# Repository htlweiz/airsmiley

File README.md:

# Air Smiley: eCO2 measurement box
A small-ish and simple box to measure
- eCO2 with a CCS811 sensor
- Temperature and Humidity with a DHT22 sensor

using a Wemos D1 mini (or clone) with visualization on a
- 0.96" I2C OLED (SSD1306 based)
- NeoPixel compatible RGB LED ring (WS2812B)

The thresholds are set according to [REHVA's recommendations for schools](https://www.rehva.eu/fileadmin/user_upload/REHVA_COVID-19_guidance_document_School_guidance_25112020.pdf).

## User Manual
A (german) user manual is available [here](AIR%20SMILEY.pdf).

## Burn-In
For full sensor accuracy, according to the [datasheet](https://www.sciosense.com/wp-content/uploads/2020/01/CCS811-Datasheet.pdf), the device first needs a "burn-in" phase of 48 operating hours. 

## Run-In
After the "burn-in" phase, the values are considered accurate after a "run-in" time of 20 minutes after power on. Make sure you expose the sensor to clean air throughout the run-in or shortly afterwards to correctly set the baseline (low CO2) for correct sensor readings.

## Flashing
- Install the newest [ESP8266 support](https://www.heise.de/ct/artikel/Arduino-IDE-installieren-und-fit-machen-fuer-ESP8266-und-ESP32-4130814.html)
- Add the following libraries (using the built-in library manager, *Tools –> Manage Libraries...*)
  - NeoPixelBus by Makuna (LGPL-3.0 License)
  - Adafruit CCS811 (MIT License)
  - DHT sensor library by Adafruit (MIT License)
  - Adafruit SSD1306 (BSD License)

## PCB
The PCB has been designed with KiCad and uses the corresponding [libraries](https://kicad.org/libraries/) which are available under the [Creative Commons CC-BY-SA 4.0 License](https://creativecommons.org/licenses/by-sa/4.0/legalcode). Additionally, a [footprint](https://github.com/rubienr/wemos-d1-mini-kicad) made by [rubienr](https://github.com/rubienr) is used.

The PCB is designed to be screwed into a case available at [aliexpress](https://de.aliexpress.com/item/4000068796385.html?spm=a2g0s.9042311.0.0.52614c4dDeY8Wv).

1

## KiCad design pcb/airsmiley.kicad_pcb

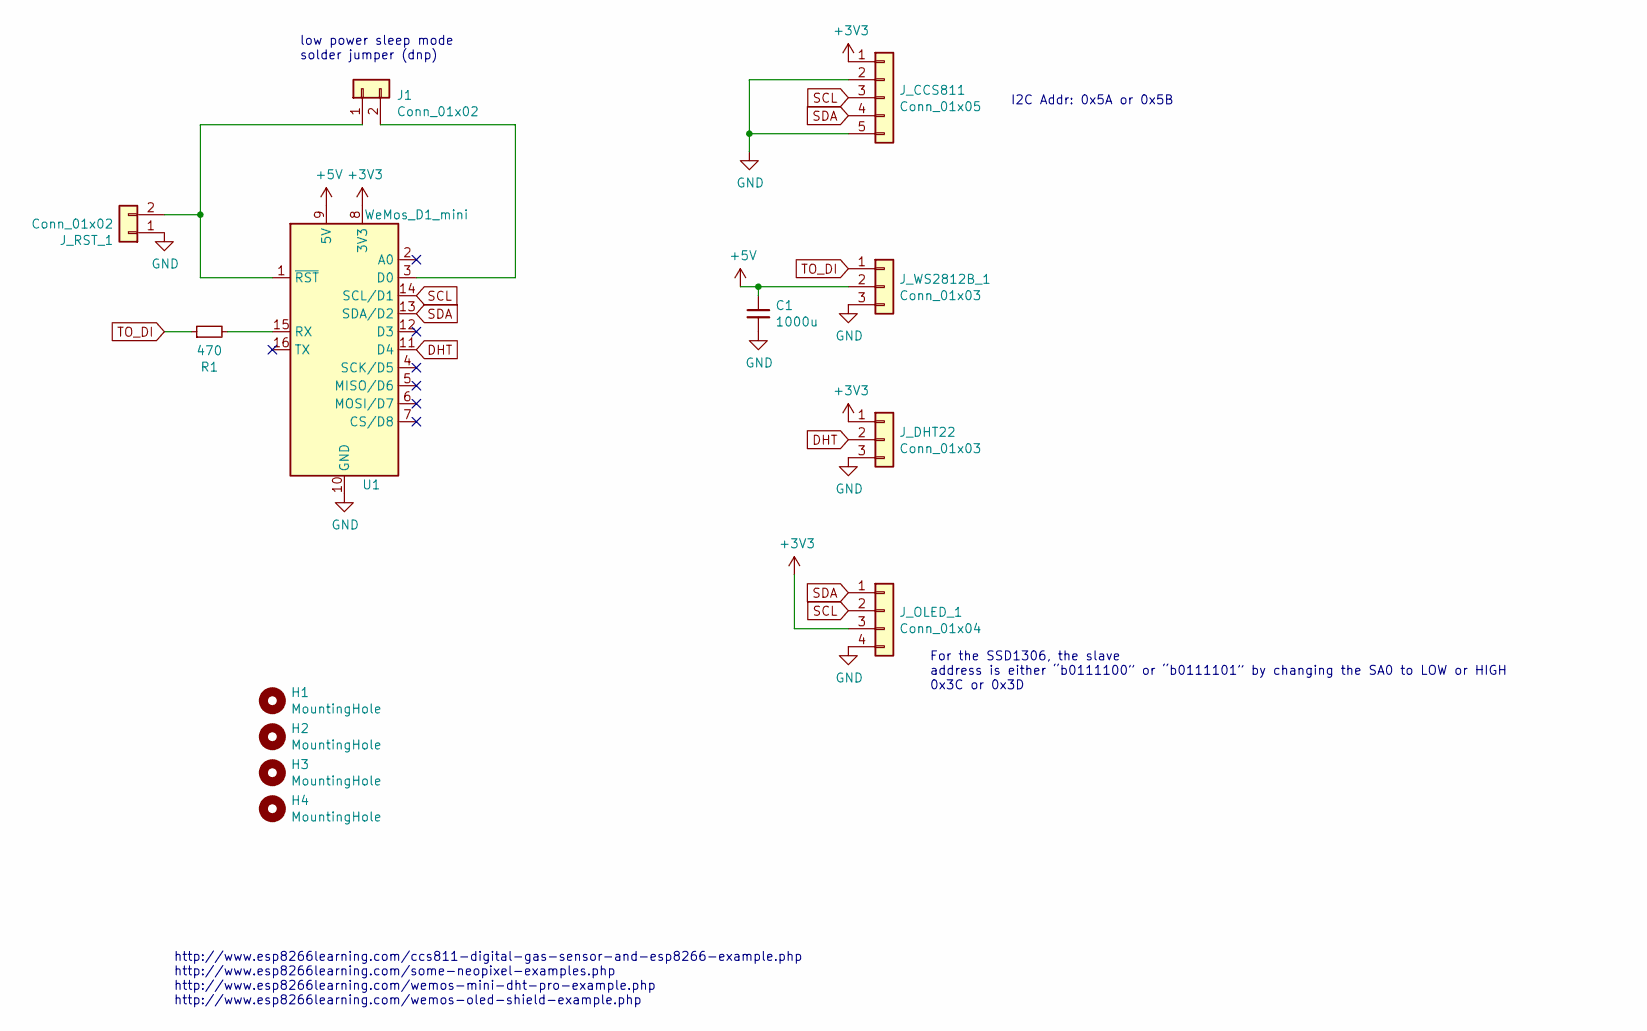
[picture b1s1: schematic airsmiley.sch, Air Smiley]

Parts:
C1: 1000u; C_Radial_D10.0mm_H12.5mm_P5.00mm
H1, H2, H3, H4: MountingHole; MountingHole_2.7mm_M2.5
J1: Conn_01x02; PinHeader_1x02_P2.54mm_Vertical
J_CCS811: Conn_01x05; PinHeader_1x05_P2.54mm_Vertical
J_DHT22: Conn_01x03; PinHeader_1x03_P2.54mm_Vertical
J_OLED_1: Conn_01x04; PinHeader_1x04_P2.54mm_Vertical
J_RST_1: Conn_01x02; PinHeader_1x02_P2.54mm_Vertical
J_WS2812B_1: Conn_01x03; PinHeader_1x03_P2.54mm_Vertical
R1: 470; R_Axial_DIN0207_L6.3mm_D2.5mm_P10.16mm_Horizontal
U1: WeMos_D1_mini; WEMOS_D1_mini_light

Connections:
+3V3: J_CCS811.1, J_DHT22.1, J_OLED_1.3, U1.8 (3V3)
+5V: C1.1, J_WS2812B_1.2, U1.9 (5V)
DHT: J_DHT22.2, U1.11 (D4)
GND: C1.2, J_CCS811.2, J_CCS811.5, J_DHT22.3, J_OLED_1.4, J_RST_1.1, J_WS2812B_1.3, U1.10 (GND)
unnamed: J1.1, J_RST_1.2, U1.1 (~RST)
unnamed: J1.2, U1.3 (D0)
unnamed: R1.2, U1.15 (RX)
SCL: J_CCS811.3, J_OLED_1.2, U1.14 (SCL/D1)
SDA: J_CCS811.4, J_OLED_1.1, U1.13 (SDA/D2)
TO_DI: J_WS2812B_1.1, R1.1

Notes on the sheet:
http://www.esp8266learning.com/ccs811-digital-gas-sensor-and-esp8266-example.php http://www.esp8266learning.com/some-neopixel-examples.php http://www.esp8266learning.com/wemos-mini-dht-pro-example.php http://www.esp8266learning.com/wemos-oled-shield-example.php
low power sleep mode solder jumper (dnp)
I2C Addr: 0x5A or 0x5B
For the SSD1306, the slave address is either “b0111100” or “b0111101” by changing the SA0 to LOW or HIGH 0x3C or 0x3D

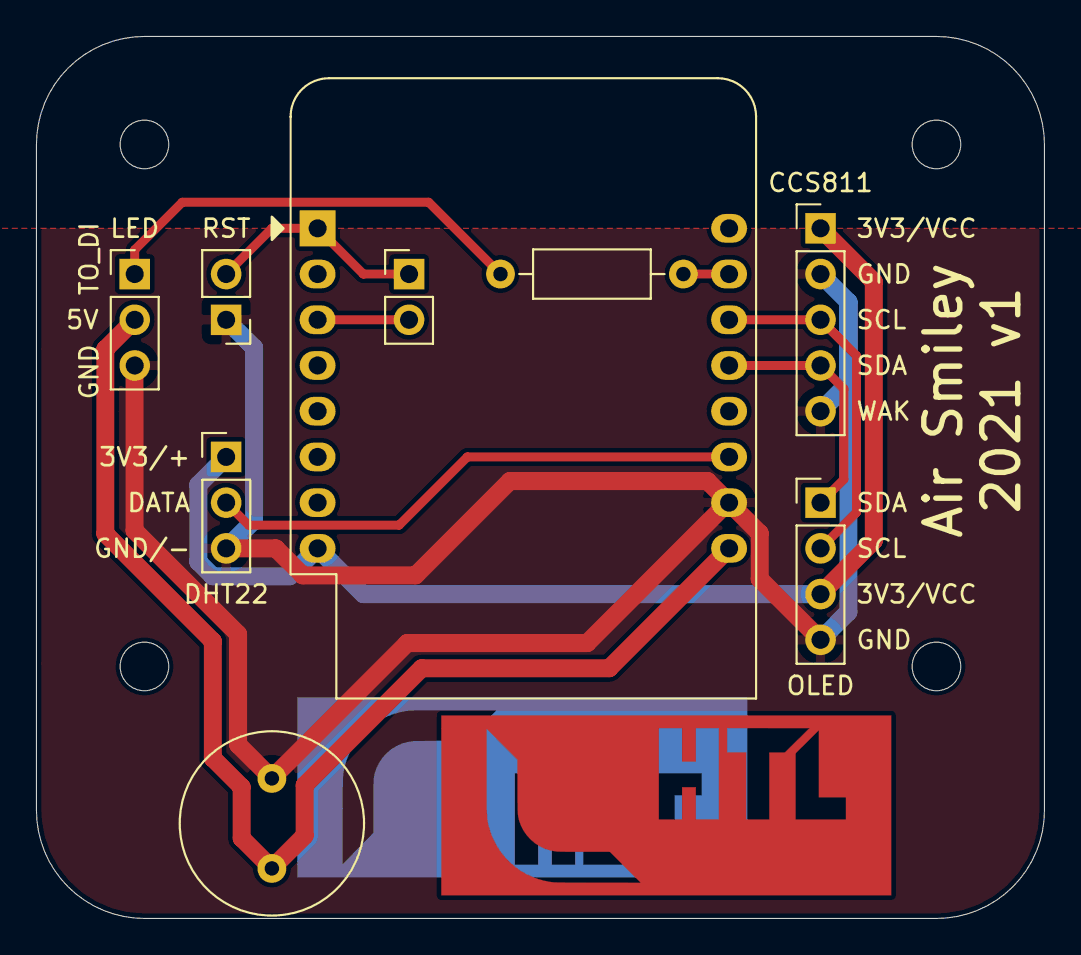
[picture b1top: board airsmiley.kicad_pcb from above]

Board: 2 copper layers, 56.0 x 49.0 mm, 15 parts (1 on the bottom side), 10 nets.

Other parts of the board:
Ref**: Val**; logo
Ref**#2: Val**; logo

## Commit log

2020-11-27 added schematic and pcb printout
2020-11-27 added 3d pcb view
2020-11-27 Updated REAMDE.md
2020-12-13 more details on sensor run-in
2020-12-13 added debug output, ran through clang-format
2021-02-13 Renamed to "Air Smiley"
2021-02-13 Fixed URL in README.md
2021-02-13 rename to "Air Smiley" in arduino code
2021-02-13 adapted license
2021-02-17 minor pcb changes
2021-04-05 added user manual
2021-04-05 added link to user manual
